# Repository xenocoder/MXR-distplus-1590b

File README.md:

MXR Distortion+ for 1590b enclosure

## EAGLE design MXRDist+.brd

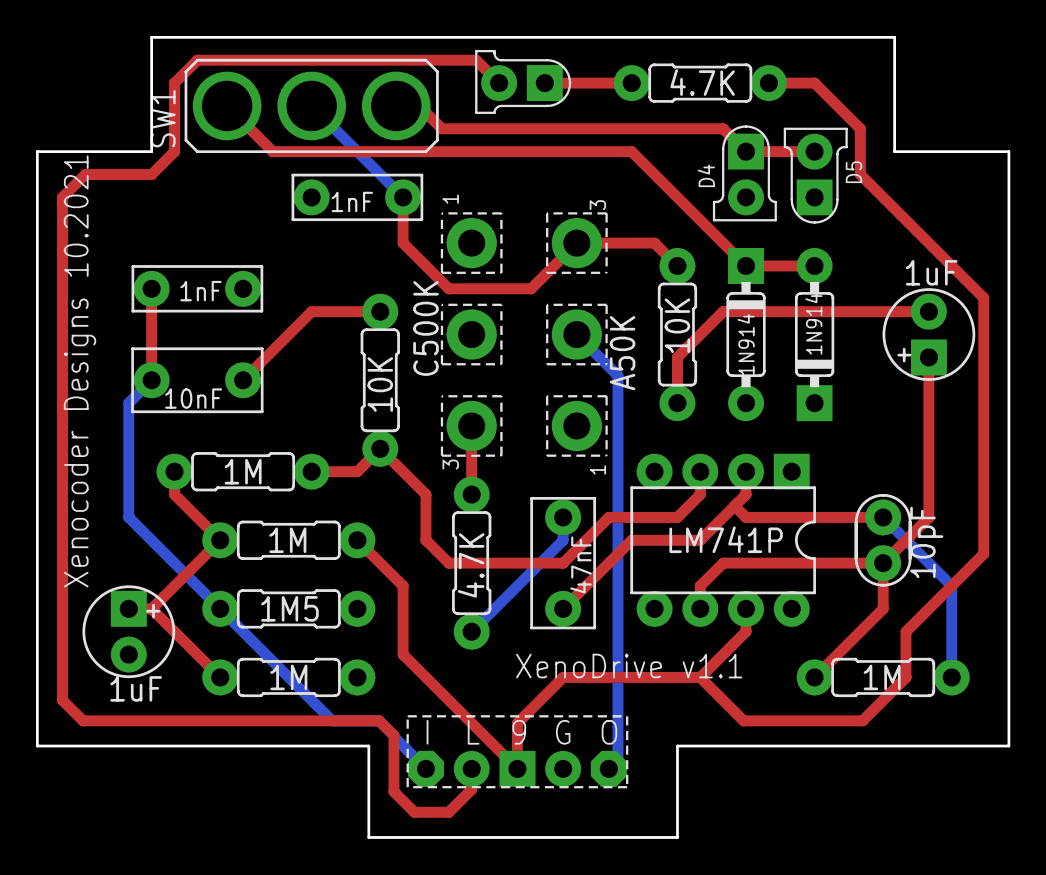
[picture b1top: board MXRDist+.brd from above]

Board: 2 copper layers, 54.0 x 44.5 mm, 26 parts (0 on the bottom side), 17 nets.

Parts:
C1, C6: 1uF; 050_020_1
C2: 10nF; 072X035
C3, C7: 1nF; 072X025
C4: 47nF; 072X035
C5: 10pF; 050X030_050_1
D1, D2: 1N914; DO35-3
D3: LED; LED3MM
D4, D5: LED3MM
IC1: LM741P; DIL08
POT1: C500K; 16MM
POT2: A50K; 16MM
R1: 1M5; R0207/3
R2, R3, R4, R8: 1M; R0207/3
R5, R9: 10K; R0207/3
R6, R7: 4.7K; R0207/3
SW1: M9040P
U$1: BOARDLINK

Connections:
GND: C1.-, C3.2, C7.2, D1.A, D2.C, D4.K, D5.A, IC1.4, POT1.1, POT1.2, POT2.1, R1.1, R3.2, U$1.4
unnamed: C1.+, R2.2, R3.1, R4.1
unnamed: IC1.3, R4.2, R5.2
unnamed: C2.1, R5.1
unnamed: POT1.3, R6.1
unnamed: C5.2, C6.+, IC1.6, R8.2
unnamed: C4.2, R6.2
unnamed: C4.1, C5.1, IC1.2, R8.1
unnamed: C6.-, R9.1
unnamed: C7.1, POT2.3, R9.2, SW1.2
unnamed: IC1.7, R2.1, R7.2, U$1.3
unnamed: C2.2, C3.1, R1.2, U$1.1
unnamed: D3.A, R7.1
unnamed: D3.K, U$1.2
unnamed: POT2.2, U$1.5
unnamed: D4.A, D5.K, SW1.3
unnamed: D1.C, D2.A, SW1.1

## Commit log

2015-10-08 Initial upload
2021-10-22 New layout with diode switch
2021-10-22 Cleanup for V1.1 release with diode switch
2025-07-05 Updated Design
2025-11-22 Adds drill guide
2025-11-22 Adds Maxcrunch CAM files
